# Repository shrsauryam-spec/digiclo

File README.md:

# <p align="center">DigiClo</p>

<p align="center">A Digital Clock with Date, Day, Temperature, and Alarm System using NodeMCU ESP8266</p>

## Why?
I do not usually use my phone, so the only way for me to know the time is with a clock or a watch. And I do not wear a watch. At the same time, I do not have a watch in my room, so I created this Digital Clock to help me find out the current time. Another thing is I have a habit of forgetting the date and the day, which isn't really great. So, this clock can help me stay up-to-date. 

## Key Features:
1. Wemos D1 Mini ESP8266 as NodeMCU (WiFi Connectivity)
2. Date, Time, Day, and Temperature Display on a 1.8-inch TFT Display
3. Alarm System using a Buzzer
4. Pomodoro Timer with a Potentiometer
5. Battery Charging with TP4056 Charging Module with Protection

## Electrical Components Required:
1. Wemos D1 Mini ESP8266
2. TFT LCD Display - 1.8" inch
3. LiPo Rechargeable Battery 2000 mAh 3.7V
4. TP4056 Charging Module with Protection

## You can find the public 3d document of OnShape below:
https://cad.onshape.com/documents/623138c9b77e6759b0f10c27/w/bd2dd186e4136b7dcbcb23ae/e/b7a90ecbf7c3d132e3466b38

## PCB
Designed in KiCad. The PCB design is simple and has zero errors.

### **Schematics**

### **PCB Design**

### **PCB Front**

### **PCB Back**

## Credits
Thanks to [Hack Club](https://hackclub.com/) for providing this amazing platform.
**Some Software We Used:**
1. [KiCad](https://www.kicad.org/) - PCB Design
2. [Onshape](https://www.onshape.com/en/) - 3d Modeling
3. [GitHub](https://github.com/) - Hosting Service

## License
MIT

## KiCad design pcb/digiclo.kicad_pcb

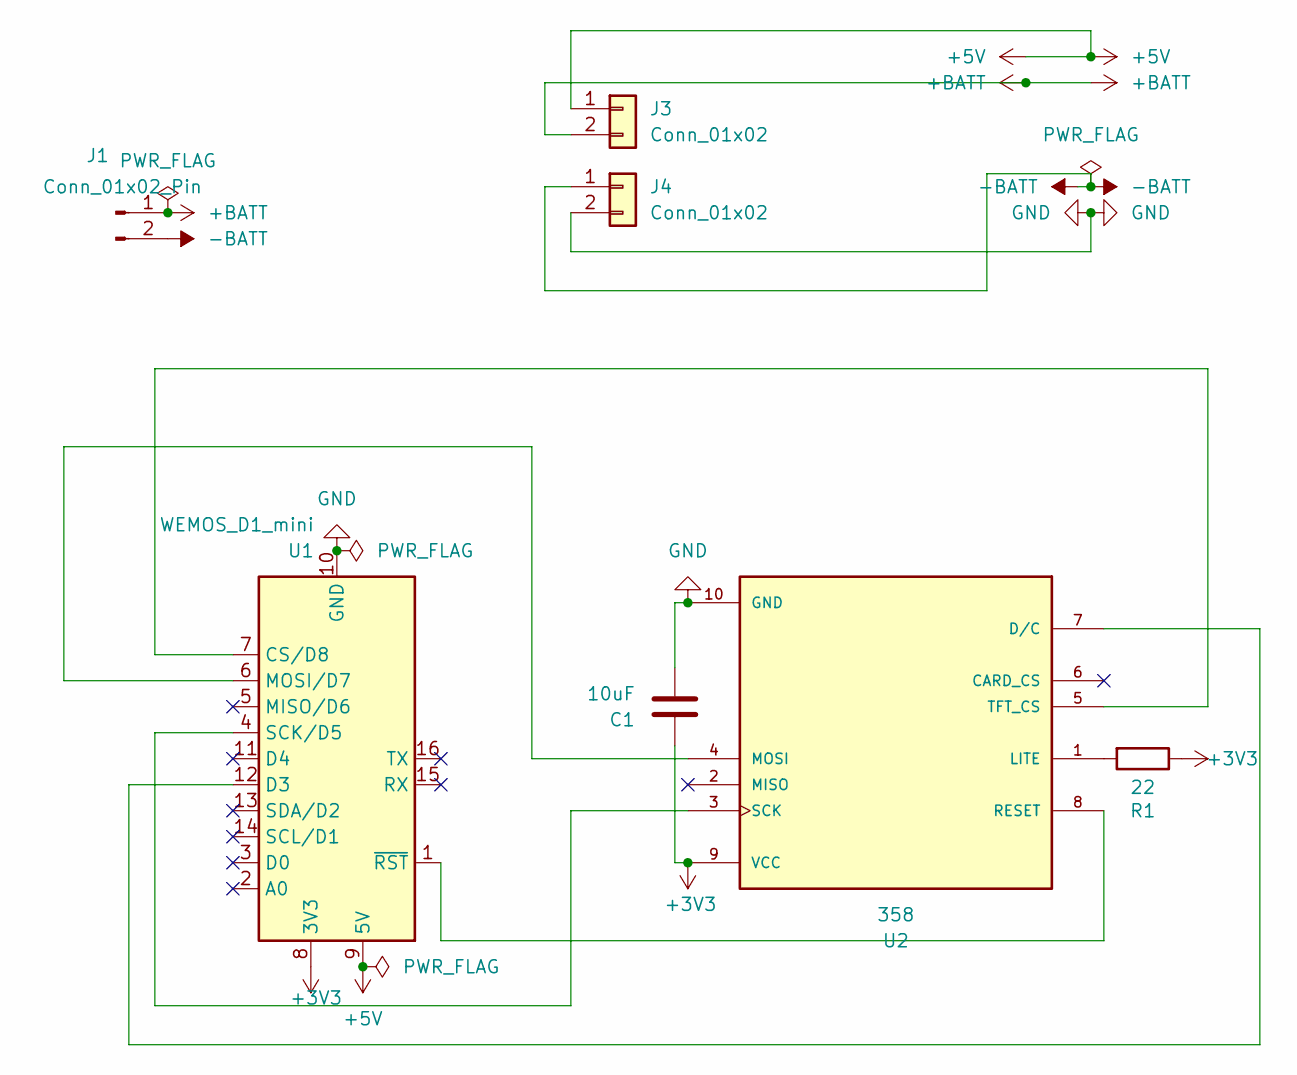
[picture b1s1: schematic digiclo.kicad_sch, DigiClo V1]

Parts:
C1: 10uF; C_0805_2012Metric_Pad1.18x1.45mm_HandSolder
J1: Conn_01x02_Pin; PinHeader_1x02_P2.00mm_Vertical
J3, J4: Conn_01x02; PinHeader_1x02_P2.54mm_Vertical
R1: 22; R_0805_2012Metric_Pad1.20x1.40mm_HandSolder
U1: WEMOS_D1_mini; WEMOS_D1_mini_light
U2: 358; MODULE_358; PARTREV 2021-12-09

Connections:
+3V3: C1.1, R1.1, U1.8 (3V3), U2.9 (VCC)
+5V: J3.1, U1.9 (5V)
+BATT: J1.1, J3.2
-BATT: J1.2, J4.1
GND: C1.2, J4.2, U1.10 (GND), U2.10 (GND)
unnamed: U1.7 (CS/D8), U2.5 (TFT_CS)
unnamed: U1.12 (D3), U2.7 (D/C)
unnamed: U1.6 (MOSI/D7), U2.4 (MOSI)
unnamed: U1.4 (SCK/D5), U2.3 (SCK)
unnamed: U1.1 (~RST), U2.8 (RESET)
unnamed: R1.2, U2.1 (LITE)

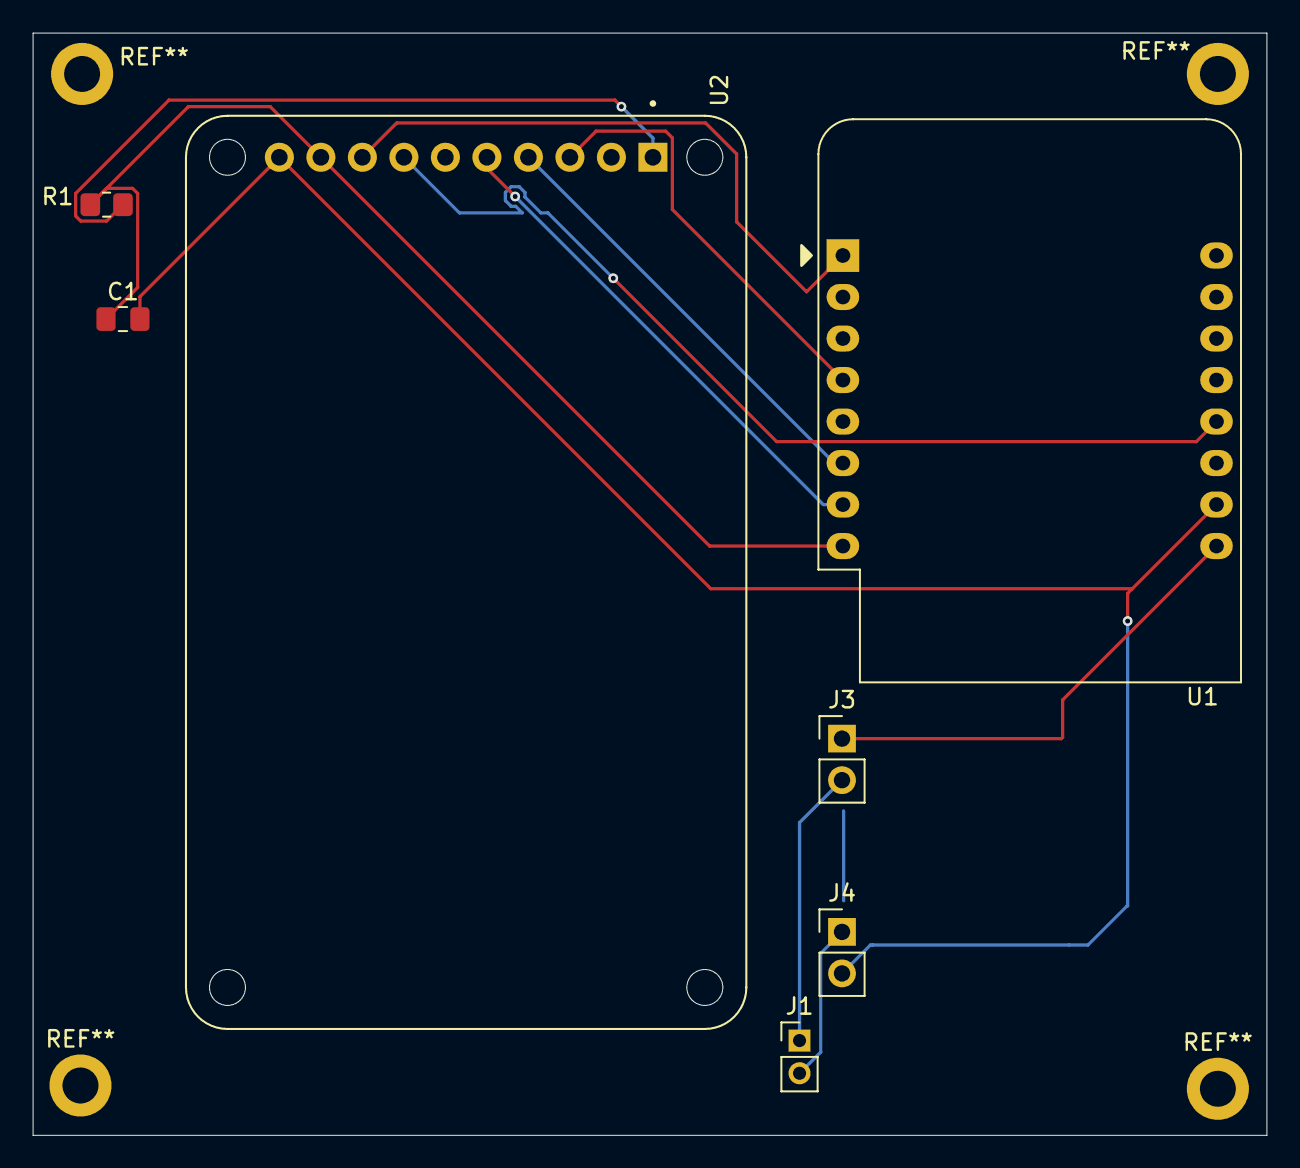
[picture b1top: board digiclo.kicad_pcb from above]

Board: 2 copper layers, 75.5 x 67.5 mm, 7 parts (0 on the bottom side), 11 nets.

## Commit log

2026-06-09 Revise README for improved clarity and content
    Updated README to enhance clarity and structure, added sections for features, components, PCB design, and credits.
2026-06-09 Add 3d models folder
2026-06-09 Add pcb folder
2026-06-09 Update README with project introduction and purpose
    Added a brief introduction and purpose for the DigiClo project.
2026-06-24 Create gitkeep
